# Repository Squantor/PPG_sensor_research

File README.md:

# PPG sensor research
This repository contains electronics, mechanical, embedded and PC side software into researching how PPG sensors work. 
## Structure
* [Electronics](https://github.com/Squantor/PPG_sensor_research/tree/master/electronics) contains the various iterations of PPG sensors
* [Software](https://github.com/Squantor/PPG_sensor_research/tree/master/software) contains the software needed for the project, either embedded or PC side software
* Scripts contain data analysis software
* Mechanical contains drawings of casing/mechanisms etc
## Checking out
This project makes extensive use of submodules, use ```git clone --recurse-submodules https://github.com/Squantor/PPG_sensor_research.git``` to clone the repository and its submodules in one go.
# Disclaimer
This project does not comprise a medical device and is not intended as such. USE AT YOUR OWN RISK!

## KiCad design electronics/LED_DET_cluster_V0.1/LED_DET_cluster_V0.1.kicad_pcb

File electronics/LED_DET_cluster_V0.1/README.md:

# Prototyping 4 LED PPG sensor cluster
Simple breakout for the 4 led PPG sensor cluster. Contains footprints for 6 leds, but a maximum of 4 can be populated, or 6 if you get creative? Just to try out various LED/sensor configurations.
## TODO's
Still some things need to be done:
* Review with one night in between
* Produce at [OSHPARK](https://oshpark.com/)
* Assemble
* Test & characterise
* update Readme.md with pictures and BOM
## BOM
* Flexible LED footprint, from 0603 LED to OSRAM PointLED (top mount)
* Flexible detector footprint, from 0603 Phototransistor to OSRAM SHF2440

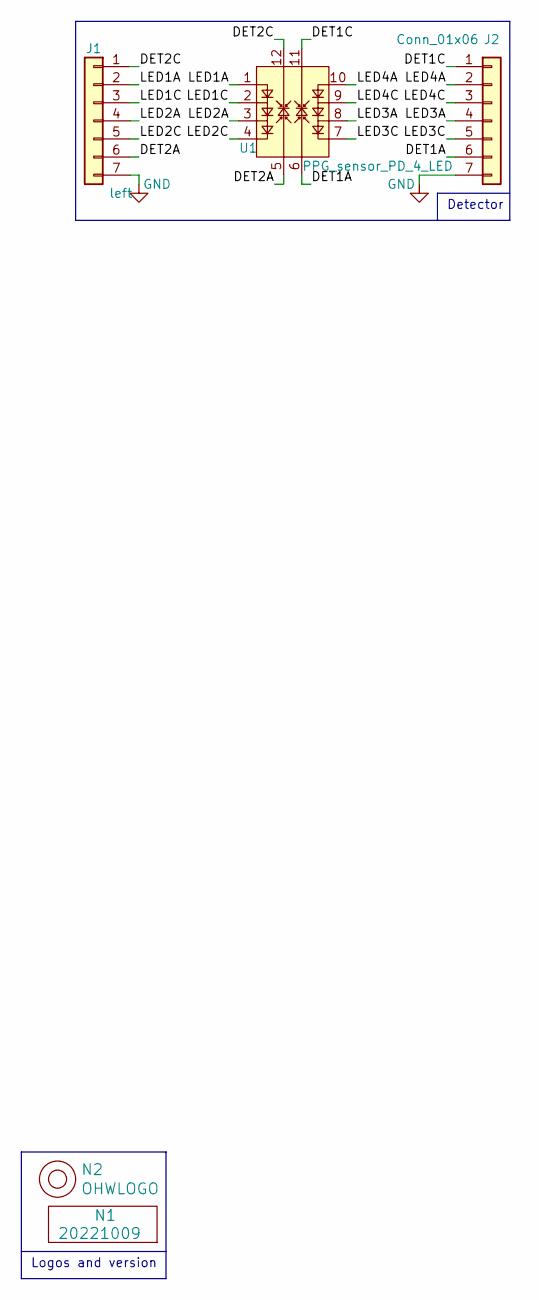
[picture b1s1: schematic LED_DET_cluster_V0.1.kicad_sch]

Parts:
J1: left; Header-0254-1X07-H010
J2: Conn_01x06; Header-0254-1X07-H010
N1: 20221009; Label_Generic
N2: OHWLOGO; OSHW-Symbol_6.7x6mm_SilkScreen
U1: PPG_sensor_PD_4_LED; PPG_sensor_4LED

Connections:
/DET1A: J2.6, U1.6
/DET1C: J2.1, U1.11
/DET2A: J1.6, U1.5
/DET2C: J1.1, U1.12
/LED1A: J1.2, U1.1
/LED1C: J1.3, U1.2
/LED2A: J1.4, U1.3
/LED2C: J1.5, U1.4
/LED3A: J2.4, U1.8
/LED3C: J2.5, U1.7
/LED4A: J2.2, U1.10
/LED4C: J2.3, U1.9
GND: J1.7, J2.7

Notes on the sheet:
Detector
Logos and version

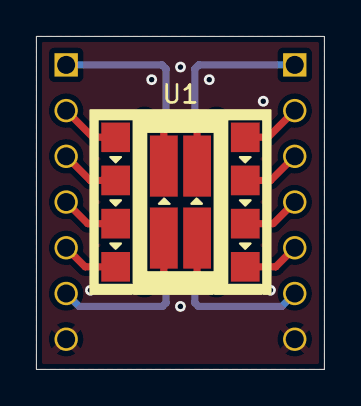
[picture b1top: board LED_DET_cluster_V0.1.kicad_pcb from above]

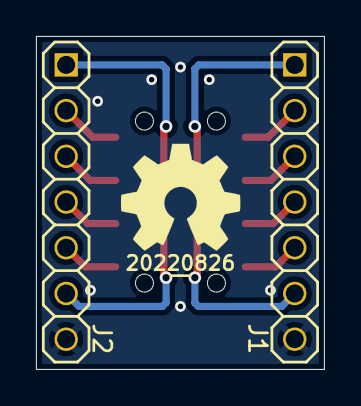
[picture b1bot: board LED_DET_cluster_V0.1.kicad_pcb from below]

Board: 2 copper layers, 16.0 x 18.5 mm, 5 parts (4 on the bottom side), 13 nets.

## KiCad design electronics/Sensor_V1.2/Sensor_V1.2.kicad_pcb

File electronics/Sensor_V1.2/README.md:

# PPG sensor hardware Version 1.2
After the lessons learned from version 1.2 it is time to simplify the hardware and explore more sensor combinations
* Try again the internal comparator but do not reserve space for this
* LPC pins broken out
* Go fully for the ADC concept, maybe via wires go to the internal comparator
* Make use of the smaller LPC824HI33 nuclone
* investigate a top only sensor without PCB cutouts with 3d printed spacers
* remove most of the superfluous hardware
# HSI (Hardware Software Interface)
What microcontroller pins are connected to what hardware and what are the needed settings
* PIO0_13 is connected to anode of LED1, should be set as output. Low turns on the LED1
* PIO0_12 is connected to anode of LED1, should be set as output. Low turns on the LED2
* PIO0_4 is connected to the gate of a transistor that resets the integrator capacitor, pulled down by a 10K resistor, should be set as output
* PIO0_25 is connected to UART receive via 100Ohm series resistor, should be set as output
* PIO0_24 is connected to UART transmit via a 100Ohm series resistor, should be set as input
* PIO0_18 is connected to the Photodiode integrator node via a normally open jumper, should be set as analog input
## TODO's
Still some things need to be done:
* Sign off to production
* Assembly
* Test & characterise, make a separate document in the documentation directory
* update Readme.md with pictures and BOM
## BOM
This design is made so flexible it accepts many different light detecting elements and LED's, some sensors/LED's tried out are are:
* [SFH2440](https://www.osram.com/ecat/DIL%20SMT%20Ambient%20Light%20Sensor%20SFH%202440/com/en/class_pim_web_catalog_103489/global/prd_pim_device_2219615/) Photodiode
* [SFH3710](https://lcsc.com/product-detail/Sensors_OSRAM_SFH3710-Z_SFH-3710-Z_C129152.html) Phototransistor
* [NCD0805G1](https://lcsc.com/product-detail/Light-Emitting-Diodes-LED_Emerald-SMDLED-Iv-220-270mcd-atIF-5mA_C84260.html) 525nm LED
* [SIR15-21C/TR8 ](https://lcsc.com/product-detail/Others_Everlight-Elec-SIR15-21C-TR8_C264405.html) 875nm IR LED
## Pictures

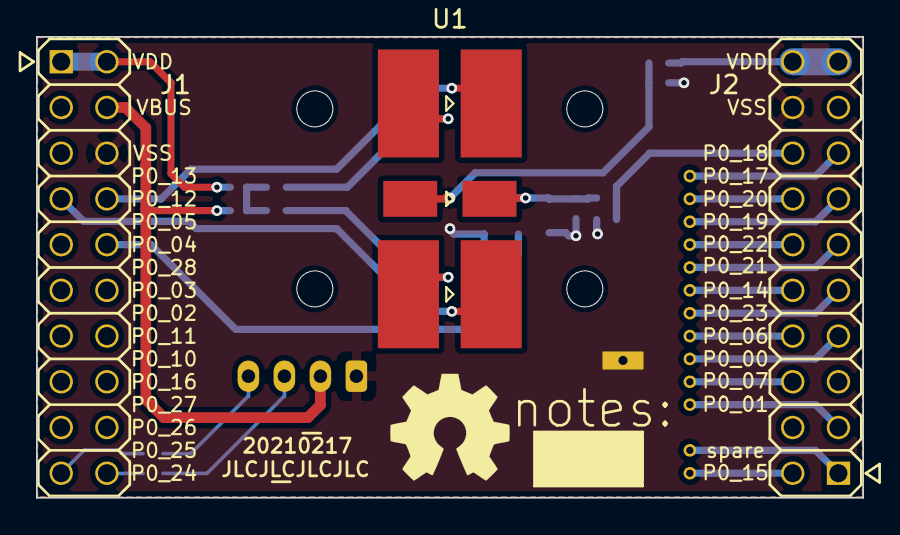
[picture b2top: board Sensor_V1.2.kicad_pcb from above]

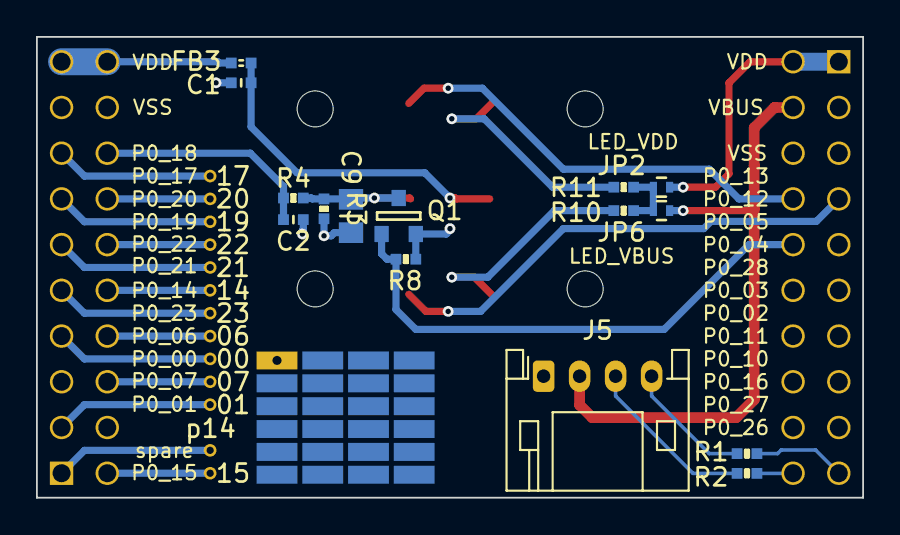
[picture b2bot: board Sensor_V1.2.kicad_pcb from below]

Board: 2 copper layers, 45.9 x 25.6 mm, 36 parts (29 on the bottom side), 30 nets.

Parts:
C1: 1u; C_0402
C2: TBD; C_0402
C9: 4n7; C_0805+0603
FB3: Ferrite_Bead; L_0402
J1: nuclone_small_left
J2: nuclone_small_right
J3: Proto_1pin; proto-SMD-0127-08X06-P010X020+pin
J5: DevBoardUartInput; JST_PH_S4B-PH-K_1x04_P2.00mm_Horizontal
JP2: LED_VDD; solder_jumper_2way_noconn
JP6: LED_VBUS; solder_jumper_2way_noconn
N1: OHWLOGO; OSHW-Symbol_6.7x6mm_SilkScreen
N2: 20210217; Label_Generic
N3: JLCJLCJLCJLC; Label_Generic
N4: notes:; Label_Note_medium
Q1: DMG1012; SOT23-3
R1, R2: 100; R_0402_hand
R3, R4: TBD; R_0402_hand
R8: 4.7K; R_0402_hand
R10, R11: 1K; R_0402_hand
TP1: 20; TestPoint_hole_H04R07
TP2: 22; TestPoint_hole_H04R07
TP3: 14; TestPoint_hole_H04R07
TP4: 06; TestPoint_hole_H04R07
TP5: 07; TestPoint_hole_H04R07
TP6: 15; TestPoint_hole_H04R07
TP7: 17; TestPoint_hole_H04R07
TP8: 19; TestPoint_hole_H04R07
TP9: 21; TestPoint_hole_H04R07
TP10: 23; TestPoint_hole_H04R07
TP11: 00; TestPoint_hole_H04R07
TP12: 01; TestPoint_hole_H04R07
TP13: p14; TestPoint_hole_H04R07
U1: PPG_sensor; PPG_sensor_front_universal

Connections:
/GPIO_14: J2.1, TP13.1
/I_reset: J1.10, Q1.1, R8.2
/LED1_A: R10.2, U1.1
/LED1_C: J1.7, U1.6
/LED2_A: R11.2, U1.3
/LED2_C: J1.8, U1.4
/LED_VDD: JP2.1, JP6.1, R10.1, R11.1
/P0_00: J2.7, TP11.1
/P0_01: J2.3, TP12.1
/P0_06: J2.8, TP4.1
/P0_07: J2.6, TP5.1
/P0_14: J2.10, TP3.1
/P0_15: J2.2, TP6.1
/P0_17: J2.15, TP7.1
/P0_19: J2.13, TP8.1
/P0_20: J2.14, TP1.1
/P0_21: J2.11, TP9.1
/P0_22: J2.12, TP2.1
/P0_23: J2.9, TP10.1
/PD_ADC: C2.2, J2.16, R4.1
/PD_BIAS: C1.2, FB3.2, U1.2
/PD_OUT: C9.1, Q1.3, R3.1, R4.2, U1.5
/UART_RX: J1.19, R1.1
/UART_TX: J1.20, R2.1
/VBUS: J1.4, J5.2, JP6.2
/VDD: J1.1, J1.2, JP2.2
/VDDA: FB3.1, J2.19, J2.20
/VSS: C1.1, C2.1, C9.2, J1.6, J2.18, J3.1, J5.1, Q1.2, R3.2, R8.1
unnamed: J5.3, R2.2
unnamed: J5.4, R1.2

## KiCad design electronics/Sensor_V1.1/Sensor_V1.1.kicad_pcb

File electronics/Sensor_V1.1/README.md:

# PPG sensor hardware Version 1.1
After the lessons learned from version 1.0 it is time to hardwire some things that have proven to be useful but also try out some other things:
* Instead of using a comparator, use an ADC to sample
* Switch from LPC812 to LPC824 board
# HSI (Hardware Software Interface)
What microcontroller pins are connected to what hardware and what are the needed settings.
* PIO0_13 is connected to the gate of a transistor that sources current for LED1, pulled down by a 10K resistor, should be set as output. High turns on the drive to LED1.
* PIO0_12 is connected to the gate of a transistor that sources current for LED2, pulled down by a 10K resistor, should be set as output. High turns on the drive to LED2.
* PIO0_4 is connected to the gate of a transistor that resets the integrator capacitor, pulled down by a 10K resistor, should be set as output
* PIO0_25 is connected to UART receive via 100Ohm series resistor, should be set as output
* PIO0_24 is connected to UART transmit via a 100Ohm series resistor, should be set as input
* PIO0_18 is connected to the Photodiode integrator node via a normally open jumper, should be set as analog input
* PIO0_17 is connected to the threshold comparator, should be set as input
## TODO's
Still some things need to be done:
* Test & characterise
* update Readme.md with pictures and BOM
## BOM
This is a list of hardware components. If just mentioned a generic component like a 1K 0402 resistor, just name it as such, free to substitute. If you need some special integrated IC's show some sources like Mouser, Digikey, Farnell, or LCSC
* [SFH2440](https://www.osram.com/ecat/DIL%20SMT%20Ambient%20Light%20Sensor%20SFH%202440/com/en/class_pim_web_catalog_103489/global/prd_pim_device_2219615/) Photodiode
* Shine through PCB mount LEDs
## Pictures

Version 1.1 PPG sensor on a LPC824HI33 nuclone board.

Closeup of the Version 1.1 PPG sensor.

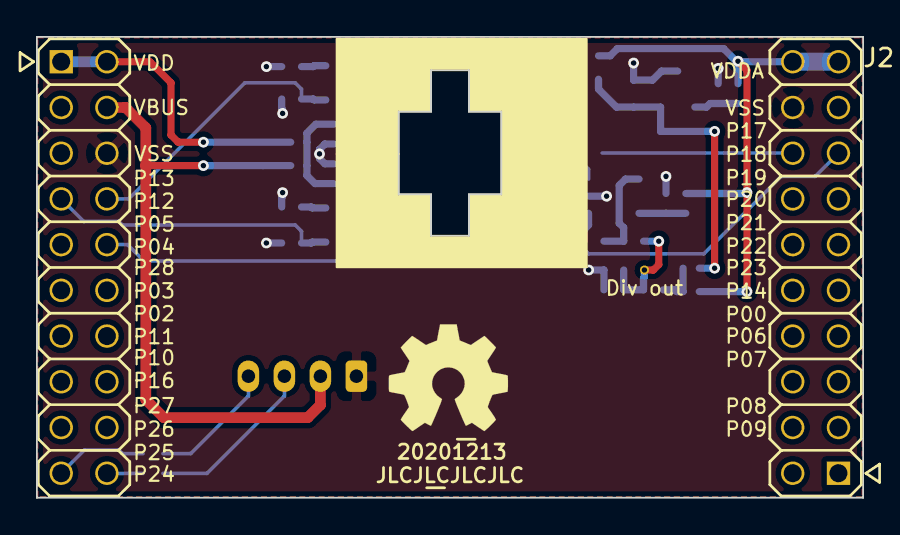
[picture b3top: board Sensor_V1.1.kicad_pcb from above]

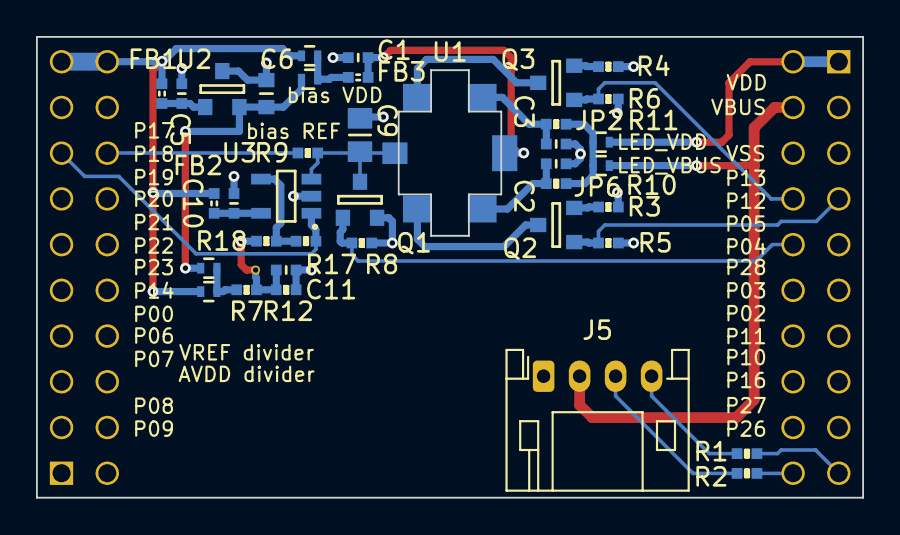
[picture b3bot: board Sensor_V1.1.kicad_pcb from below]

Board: 2 copper layers, 45.9 x 25.6 mm, 44 parts (37 on the bottom side), 29 nets.

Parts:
C1, C5, C10, C11: 1u; C_0402
C2, C3: 100n; C_0402
C6: 10u; C_0603
C9: 4n7; C_0805+0603
FB1, FB2, FB3: Ferrite_Bead; L_0402
J1: nuclone_small_left; Header-0254-2X10-H010
J2: nuclone_small_right; Header-0254-2X10-H010
J5: DevBoardUartInput; JST_PH_S4B-PH-K_1x04_P2.00mm_Horizontal
JP1: bias VDD; solder_jumper_2way_noconn
JP2: LED_VDD; solder_jumper_2way_noconn
JP3: bias REF; solder_jumper_2way_noconn
JP4: AVDD divider; solder_jumper_2way_noconn
JP5: VREF divider; solder_jumper_2way_noconn
JP6: LED_VBUS; solder_jumper_2way_noconn
N1: OHWLOGO; OSHW-Symbol_6.7x6mm_SilkScreen
N2: 20201213; Label_Generic
N3: JLCJLCJLCJLC; Label_Generic
Q1, Q2, Q3: DMG1012; SOT23-3
R1, R2, R3, R4: 100; R_0402_hand
R5, R6: 10K; R_0402_hand
R7, R12, R17, R18: R; R_0402_hand
R8: 100K; R_0402_hand
R9: 0; R_0402_hand
R10, R11: 1K; R_0402_hand
TP11: Div out; TestPoint_hole_H03R05
U1: PPG_sensor; PPG_sensor_reverse_PD_antiparallel
U2: reference_sot23-3; SOT23-3
U3: MCP6541; SOT23-5-Microchip-OT

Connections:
/CMP_OUT: J2.15, R17.1, U3.1
/Divider_out: C11.2, R7.1, R12.2, R18.1, TP11.1
/I_reset: J1.10, Q1.1, R8.2
/LED1_A: C2.1, R10.2, U1.1
/LED1_C: Q2.3, U1.6
/LED1_EN: J1.7, Q2.1, R5.2
/LED2_A: C3.1, R11.2, U1.3
/LED2_C: Q3.3, U1.4
/LED2_EN: J1.8, Q3.1, R6.2
/LED_VDD: JP2.1, JP6.1, R10.1, R11.1
/PD_ADC: J2.16, R9.2
/PD_BIAS: C1.2, FB3.2, U1.2
/PD_OUT: C9.1, Q1.3, R9.1, U1.5, U3.3
/UART_RX: J1.19, R1.1
/UART_TX: J1.20, R2.1
/VBUS: J1.4, J5.2, JP6.2
/VDD: J1.1, J1.2, JP2.2
/VDDA: FB1.1, FB2.1, J2.19, J2.20, JP1.1, JP4.1
/VREF: C6.1, JP3.1, JP5.1, U2.2
/VSS: C1.1, C2.2, C3.2, C5.2, C6.2, C9.2, C10.2, C11.1, J1.6, J2.18, J5.1, Q1.2, R3.2, R4.2, R5.1, R6.1, R8.1, R12.1, U2.3, U3.2
unnamed: C5.1, FB1.2, U2.1
unnamed: C10.1, FB2.2, U3.5
unnamed: FB3.1, JP1.2, JP3.2
unnamed: J5.3, R2.2
unnamed: J5.4, R1.2
unnamed: JP4.2, JP5.2, R7.2
unnamed: Q2.2, R3.1
unnamed: Q3.2, R4.1
unnamed: R17.2, R18.2, U3.4

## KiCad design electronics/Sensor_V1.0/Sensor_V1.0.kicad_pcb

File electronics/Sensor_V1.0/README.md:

# PPG sensor hardware Version 1.0
After making a raw prototype where some tests have been done it is time to make a PCB version.
# HSI (Hardware Software Interface)
This applies to a project that has a embedded software component. Describe what each pin/bus does, what it is connected to, what its function is and some "safe" behaviour when starting up.
## TODO's
Still some things need to be done:
* Further filling in this project description.
* schematic entry 
* PCB layout
* Review with one night in between
* Produce at [OSHPARK](https://oshpark.com/)
* Assemble
* Test & characterise
* update Readme.md with pictures and BOM
## BOM
This is a list of hardware components. If just mentioned a generic component like a 1K 0402 resistor, just name it as such, free to substitute. If you need some special integrated IC's show some sources like Mouser, Digikey, Farnell, or LCSC
* [SFH2440](https://www.osram.com/ecat/DIL%20SMT%20Ambient%20Light%20Sensor%20SFH%202440/com/en/class_pim_web_catalog_103489/global/prd_pim_device_2219615/) Photodiode
* Shine through PCB mount LEDs
## Pictures
## Measurement results

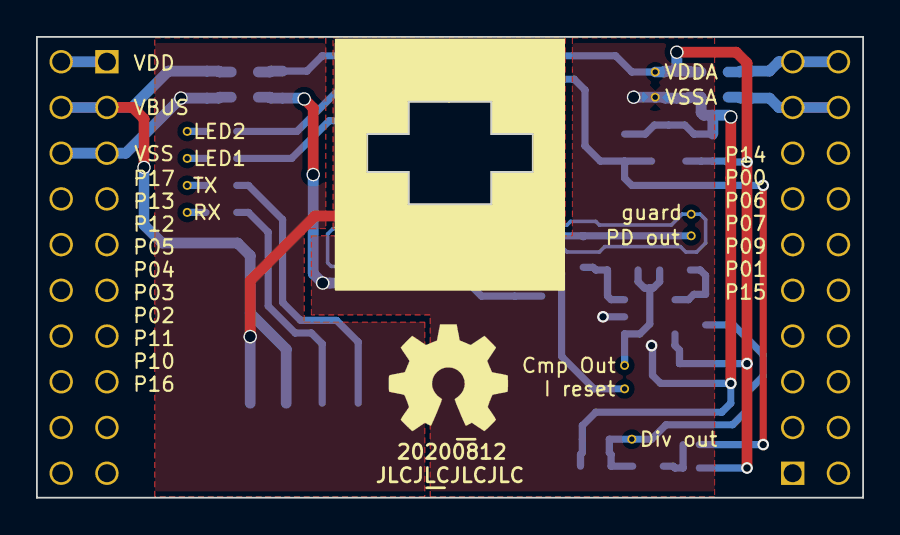
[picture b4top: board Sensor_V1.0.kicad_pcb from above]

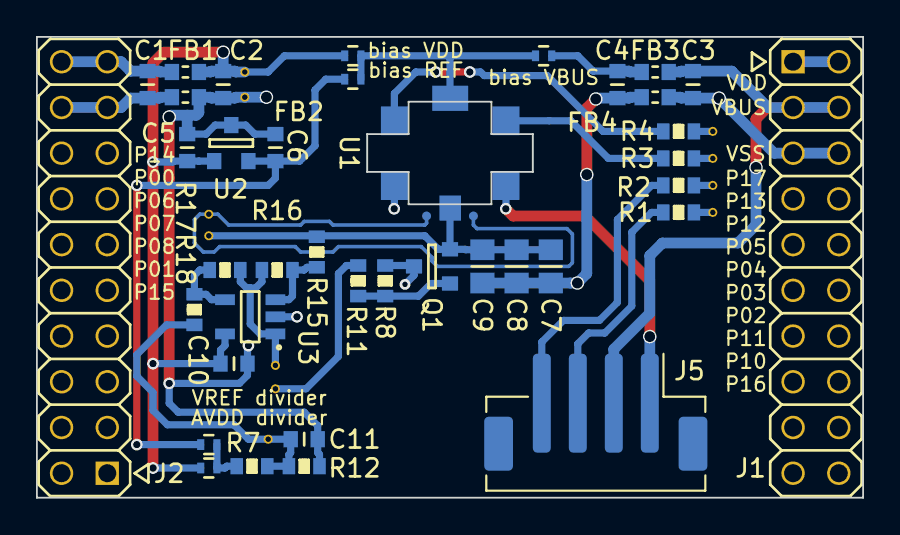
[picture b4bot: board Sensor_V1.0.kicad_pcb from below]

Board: 2 copper layers, 45.9 x 25.6 mm, 55 parts (40 on the bottom side), 27 nets.

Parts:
C1, C3, C5, C10, C11: 1u; C_0603
C2, C4, C6: 10u; C_0603
C7, C8, C9: 4n7; C_0805+0603
FB1, FB2, FB3, FB4: 600; L_0603
J1: nuclone_small_left; Header-0254-2X10-H010
J2: nuclone_small_right; Header-0254-2X10-H010
J5: DevBoardUartInput; JST_PH_B4B-PH-SM4-TB_1x04-1MP_P2.00mm_Vertical
JP1: bias VDD; solder_jumper_2way_noconn
JP2: bias VBUS; solder_jumper_2way_noconn
JP3: bias REF; solder_jumper_2way_noconn
JP4: AVDD divider; solder_jumper_2way_noconn
JP5: VREF divider; solder_jumper_2way_noconn
N1: OHWLOGO; OSHW-Symbol_6.7x6mm_SilkScreen
N2: 20200812; Label_Generic
N3: JLCJLCJLCJLC; Label_Generic
Q1: BC846; SOT23-3
R1, R2: 100; R_0603_hand
R3, R4: 1K; R_0603_hand
R7, R12, R15, R16, R17, R18: R; R_0603_hand
R8: 100K; R_0603_hand
R11: 4K7; R_0603_hand
TP1: RX; TestPoint_hole_H03R05
TP2: TX; TestPoint_hole_H03R05
TP3: LED1; TestPoint_hole_H03R05
TP4: LED2; TestPoint_hole_H03R05
TP5, TP6: guard; TestPoint_pad_circle_D05
TP7: VDDA; TestPoint_hole_H03R05
TP8: VSSA; TestPoint_hole_H03R05
TP9: guard; TestPoint_hole_H03R05
TP10: PD out; TestPoint_hole_H03R05
TP11: Div out; TestPoint_hole_H03R05
TP12: I reset; TestPoint_hole_H03R05
TP13: Cmp Out; TestPoint_hole_H03R05
U1: PPG_sensor; PPG_sensor_reverse_PD_antiparallel
U2: reference_sot23-3; SOT23-3
U3: MCP6541; SOT23-5-Microchip-OT

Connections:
/CMP_OUT: R16.2, R17.1, TP13.1, U3.1
/Divider_out: C11.2, R7.1, R12.2, R18.1, TP11.1
/I_reset: R11.2, TP12.1
/LED1: R3.1, U1.1
/LED2: R4.1, U1.3
/PD_BIAS: JP1.2, JP2.2, JP3.2, U1.2
/PD_OUT: C7.1, C8.1, C9.1, Q1.2, R15.2, TP10.1, U1.5
/PD_OUT_GUARD: TP5.1, TP6.1, TP9.1
/UART_RX: R1.1, TP1.1
/UART_TX: R2.1, TP2.1
/VBUS: C3.1, FB3.2, J1.3, J1.4, J5.2
/VDD: J1.1, J1.2
/VDDA: C2.1, C5.1, C10.1, FB1.1, JP1.1, JP4.1, TP7.1, U2.1, U3.5
/VDDA_RAW: C1.1, FB1.2, J2.19, J2.20
/VREF: C6.1, JP3.1, JP5.1, U2.2
/VSS: C3.2, FB4.2, J1.5, J1.6, J5.1, U1.4, U1.6
/VSSA: C2.2, C4.2, C5.2, C6.2, C7.2, C8.2, C9.2, C10.2, C11.1, FB2.1, FB4.1, Q1.3, R8.1, R12.1, TP8.1, U2.3, U3.2
/VSSA_RAW: C1.2, FB2.2, J2.17, J2.18
unnamed: C4.1, FB3.1, JP2.1
unnamed: J5.3, R1.2
unnamed: J5.4, R2.2
unnamed: JP4.2, JP5.2, R7.2
unnamed: Q1.1, R8.2, R11.1
unnamed: R3.2, TP3.1
unnamed: R4.2, TP4.1
unnamed: R15.1, R16.1, U3.3
unnamed: R17.2, R18.2, U3.4

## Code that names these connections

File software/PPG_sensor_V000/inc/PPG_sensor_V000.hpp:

/*
MIT License

Copyright (c) 2019 Bart Bilos

Permission is hereby granted, free of charge, to any person obtaining a copy
of this software and associated documentation files (the "Software"), to deal
in the Software without restriction, including without limitation the rights
to use, copy, modify, merge, publish, distribute, sublicense, and/or sell
copies of the Software, and to permit persons to whom the Software is
furnished to do so, subject to the following conditions:

The above copyright notice and this permission notice shall be included in all
copies or substantial portions of the Software.

THE SOFTWARE IS PROVIDED "AS IS", WITHOUT WARRANTY OF ANY KIND, EXPRESS OR
IMPLIED, INCLUDING BUT NOT LIMITED TO THE WARRANTIES OF MERCHANTABILITY,
FITNESS FOR A PARTICULAR PURPOSE AND NONINFRINGEMENT. IN NO EVENT SHALL THE
AUTHORS OR COPYRIGHT HOLDERS BE LIABLE FOR ANY CLAIM, DAMAGES OR OTHER
LIABILITY, WHETHER IN AN ACTION OF CONTRACT, TORT OR OTHERWISE, ARISING FROM,
OUT OF OR IN CONNECTION WITH THE SOFTWARE OR THE USE OR OTHER DEALINGS IN THE
SOFTWARE.
*/
#ifndef PPG_SENSOR_V000_HPP
#define PPG_SENSOR_V000_HPP

#define IOCON_XTAL_IN       IOCON_PIO8
#define IOCON_XTAL_OUT      IOCON_PIO9

#define IOCON_LED_CTRL      IOCON_PIO12
#define PIN_LED_CTRL        (12u)
#define IOCON_CAP_SENSE     IOCON_PIO0
#define PIN_CAP_SENSE       (0u)
#define IOCON_CMP_OUT       IOCON_PIO7
#define PIN_CMP_OUT         (7u)
#define IOCON_CAP_RESET     IOCON_PIO14
#define PIN_CAP_RESET       (14u)
#define IOCON_VDDCMP        IOCON_PIO6
#define PIN_VDDCMP          (6u)

#define IOCON_UART_TX       IOCON_PIO13
#define PIN_UART_TX         (13u)
#define IOCON_UART_RX       IOCON_PIO17
#define PIN_UART_RX         (17u)

#define UART_DEBUG          LPC_USART0
#define UART_BAUD_RATE      (500000u)

#define CLOCK_MAIN_SOURCE   SYSCTL_MAINCLKSRC_PLLOUT

#define CLOCK_XTAL          (12000000u)
#define CLOCK_EXT_IN        (0u)
#define CLOCK_CPU           (30000000u)
#define CLOCK_AHB           (30000000u)
#define CLOCK_MAIN          (60000000u)

void boardInit(void);

void boardPpgLedState(bool on);

#endif

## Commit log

2020-07-08 initial description
2020-07-08 updated URL
2020-07-08 added initial project
2020-07-08 updated Readmes
2020-07-08 PPG sensor LED blink now
2020-08-02 WIP SCT setup
2020-08-02 updated to new buildsystem with doxygen generation
2020-08-02 updated to newer libmcull
2020-08-02 added vscode task for building the documentation
2020-08-02 removing old stuff and start with blink initiated by the SCT
2020-08-02 LED control functional at 30HZ
2020-08-02 added capacitor reset output
2020-08-03 added capacitor sensing pin
2020-08-03 removed defunct function
2020-08-03 disabled pullup on cap sensing pin, initialised comparator input, preparation for integrator reset transistor
2020-08-03 inreased led duty cycle
2020-08-03 added integrator reset output
2020-08-03 first setup of analog comparator
2020-08-03 newer libmcull
2020-08-03 added comparator output intermediate pin, used as SCT input
2020-08-03 comparator control of LED duration
2020-08-03 newer libmcull with capture functions
2020-08-03 WIP comparator capture
2020-08-04 updated to new libmcull
2020-08-04 added capture functionality
2020-08-04 fixed error in setup
2020-08-04 added newer function
2020-08-04 added printing of sensor values, but there is some noise, time for a proper proto?
2020-08-05 moved to different analog comparator API
2020-08-05 added newer ladder reference value that more matches the internal reference
2020-08-06 Powered resistor ladder with VDD directly instead of internal VDD
2020-08-07 switched to external divider instead of internal one, much lower noise
2020-08-08 added sensor electronics version V1.0
2020-08-08 added PCB library
2020-08-08 WIP schematic definition
2020-08-09 added LED drive connections, started with PPG sensor connections
2020-08-09 updated pcb library
2020-08-09 done with PPG sensor nodes, working on PD bias supply selection
2020-08-09 small update
2020-08-09 completed PD bias
2020-08-09 updated with new PPG footprint
2020-08-09 WIP some layout and additional testpoints
2020-08-09 WIP more layout and extra testpoints added, next step are my own testpoints, those from kicad are just annoying
2020-08-09 added newer testpoints
2020-08-09 updated testpoints to something smaller
2020-08-09 WIP some placement and component changes
2020-08-09 added additional pad
2020-08-09 changed some testpads, some futher placement
2020-08-09 added integrator capacitor and reset, WIP resistor divider
2020-08-09 added resistor divider
2020-08-09 some placement optimizations and minor routing
2020-08-09 further compaction
2020-08-09 forgot to commit some component definitions
2020-08-09 updated pcb library, added comparator bits, some placement and debugging ERC errors
2020-08-09 fixed ERC errors
2020-08-09 WIP comparator section and final fixes for ERC
2020-08-09 added a SCT timeout event
2020-08-10 updated versionnumber, added decoupling capacitor on resistor network
2020-08-10 added resistor network decoupling capacitpr
2020-08-10 added ground plane(s)
2020-08-10 updated some more placement
2020-08-11 simplified resistor divider, I have E24 range at home, no need to mess with series/parallel combinations
2020-08-11 WIP layout
2020-08-11 routing completed
2020-08-11 more silk placements
2020-08-11 added mask opening for guard trace
2020-08-11 beautified position a bit (ordering of capacitor to be incrementing
2020-08-11 updated versionnumber
2020-08-12 small changes
2020-08-12 fixed test pad
2020-08-12 added 3d models to a few components
2020-08-12 minor changes, reverted default line thickness
2020-08-12 refilled zones
2020-08-12 moved test points a bit out of the way of the sensor
2020-08-20 started with bringup of PPG sensor V1.0
2020-08-20 same functionality now for PPG sensor V1.0
2020-08-21 upped the baud rate
2020-08-21 moved integrator reset to SCT output 2
2020-08-21 added now two outputs for the SCT LED's
2020-08-23 trying some fixes for lost capture problem
2020-08-24 noise debugging of PPG sensor
2020-08-25 baud rate increase to facilitate higher sampling rate
2020-08-25 reduced printing output
2020-08-25 switched to single led drive
2020-08-25 increased sampling rate and reduced the integrator reset period after changing base drive resistor
2020-08-26 set sampling frequency to 30Hz and using external comparator
2020-09-08 copied Version 1.0 to version 1.1 hardware
2020-09-08 newer PCB library
2020-09-08 started with schematic modifications
2020-09-08 minor layout changes and component swaps
2020-09-18 updated PCB component library
2020-09-18 placement and some routing of led drive circuitry
2020-09-18 modified integrator bits
2020-09-18 initial placement of some components
2020-10-01 schematic modifications and cleanup
2020-10-01 easier routing of UART pins
2020-10-01 updated layout and started with starground/VDDA
2020-10-01 WIP PCB labels
2020-10-18 added PD net ties, more ties needed
2020-10-18 net ties for comparator
2020-10-18 starting to move analog stuff to VSSA and then to star grounds/vcc's. imported net ties
2020-10-31 undoing most of the net splitting for a star VSS/VDD
2020-10-31 added ADC sampling connection
2020-10-31 annotated components
2020-10-31 added some ferrite beads
2020-10-31 added annotations
2020-10-31 added all noconnects, fixed ERC errors
2020-11-06 added PD bias decoupling and ferrite bead
2020-11-06 Added annotated components
2020-12-11 adapted LED drive circuit
2020-12-11 fixed DRC errors
2020-12-11 fixed a small mistake with decoupling and ferrites
2020-12-11 placement of components
2020-12-13 changed the led drive shunt to be ground referenced
2020-12-13 updated schematic into PCB
2020-12-13 placed LED drive
2020-12-13 changed integrator capacitor size to something smaller
2020-12-13 again updated integrator capacitor footprint
2020-12-13 placed more parts on the integrator/comparator side
2020-12-13 placed resistor divider and voltage reference
2020-12-13 fixed DRC issues
2020-12-13 further silk screen placement of the reference, bias arrangement and photodiode integrator
2020-12-13 removed some pin labels that overlapped too much
2020-12-13 wrong header placement
2020-12-13 schanged UART RX/TX pinning due to flipped connector
2020-12-13 renaming labels, fixxing some routing
2020-12-13 fixed labels on the left side
2020-12-13 fixed labels on right hand connector
2020-12-13 silk placement updates
2020-12-15 silk changes, component placement changed, replaced PD ADC connection with a jumper
2021-01-23 updated submodules and added libembedded
2021-01-26 updated to new build system
2021-01-26 updated to newer buildsystem
2021-01-26 updated doxyfile
2021-01-26 moved over blinky for nuclone LPC824DH20 to PPG sensor V1.1
2021-01-26 moved to different nuclone board name
2021-01-27 updated build environment
2021-01-27 adapted debugging script
2021-01-28 renamed header board file
2021-01-28 updated hardware description
2021-01-28 added pin configuration according to HSI
2021-01-28 ported V100 PPG sensor code to V110
2021-01-28 fixed crystaloscillator issue, tried to get the SCT going but does not work, yet
2021-01-29 added input muxing to make the SCT work, added some more comments
2021-01-29 updated libMcuLL
2021-01-29 added a bunch of debugging scripts
2021-01-29 removed non functional debugging scripts
2021-01-29 added some documentation, eliminated some code
2021-01-30 started with splitting up PPG sensor code
2021-01-30 updated license block
2021-01-30 added initial boilerplate include stuff
2021-01-30 split up the PPG sensor code into a separate module
2021-02-07 added post build step to generate disassembly
2021-02-07 removed old submodule
2021-02-07 removed defunct submodule
2021-02-07 updated to newer libEmbedded, it has all the things from squantorlibembeddedC
2021-02-12 updated changed toolchain and incorrect include path
2021-02-12 updated libembedded to add circular buffer and moving average filter
2021-02-12 removing settings from git and adding to gitignore
2021-02-12 added bugfixed moving average filter C variant
2021-02-12 added ringbuffer sample caching and moving average filter for noise filtering
2021-02-12 integrator reset shortened
2021-02-12 added templated ringbuffer and moving average filter
2021-02-13 changed moving average filter depth
2021-02-13 started initial project for PPG sensor V1.2
2021-02-13 removing comparator based PPG sensor
2021-02-13 copied over stuff from comparator based PPG sensor to the ADC one and switched build to that
2021-02-13 fixed build error switching from comparator PPG to ADC PPG
2021-02-13 reduced PPG sensor blink rate to make visual identification easier during debugging the SCT
2021-02-13 made LED turn ond and off at a fixed blink rate
2021-02-13 changed frequency and on times
2021-02-14 added ADC calibration
2021-02-14 initial implementation of ADC sampling
2021-02-14 got interrupts working but no valid ADC values, yet
2021-02-14 returned sampling rate to something more normal
2021-02-14 changed timing and some names
2021-02-14 revisited and made V000 working
2021-02-14 copied over V1.1 to V1.2 sensor
2021-02-14 imported newer named small LPC824 schematic component
2021-02-14 added testpoints
2021-02-14 passing ERC, added test pad section, added RC to ADC input
2021-02-14 imported some changed components, but need to redo the footprints from TODO
2021-02-15 removed old library
2021-02-15 finished schematic and passes ERC
2021-02-15 initial placement of components
2021-02-15 updated pcb library with test pads and ppg sensor
2021-02-15 removed broken symbol library
2021-02-15 updated versionnumber, added prototyping area, changed connectors
2021-02-15 not enough space for prototyping area
2021-02-15 updated with smaller prototyping area
2021-02-15 newer library
2021-02-15 components placed, changing silk
2021-02-15 added prototyping area
2021-02-15 changed header labels, changed test point labels
2021-02-15 rerouting/re-placement of components
2021-02-16 small clarification changes
2021-02-16 completed PCB silk placement
2021-02-17 updated readme state
2021-02-17 added notes field, updated versionnumber
2021-02-17 updated moving average template
2021-02-17 added some additional channels, increased baud rate for serial studio, integrated moving average with settable reset average
2021-02-17 added serial studio 2 channel json
2021-02-17 defined ADC bounds, moved some algorithm stuff to main
2021-02-17 added extra channel for the LED on time, added automatic LED scaling to keep the ADC value centered
2021-02-17 adjusted some LED on times
2021-02-19 making V000 suitable for serial studio
2021-02-25 added kicad output plots to ignore
2021-02-25 added plotting outputs
2021-02-25 changed plot directory
2022-08-26 updated git module addresses to ssh
2022-08-26 started with PPG detector cluster project
2022-08-26 updated gitignore
2022-08-26 completed LED detector cluster 0.1
2022-08-27 updating sensor cluster breakout
2022-10-07 updated pcb element
2022-10-09 updated PPG LED detector cluster
